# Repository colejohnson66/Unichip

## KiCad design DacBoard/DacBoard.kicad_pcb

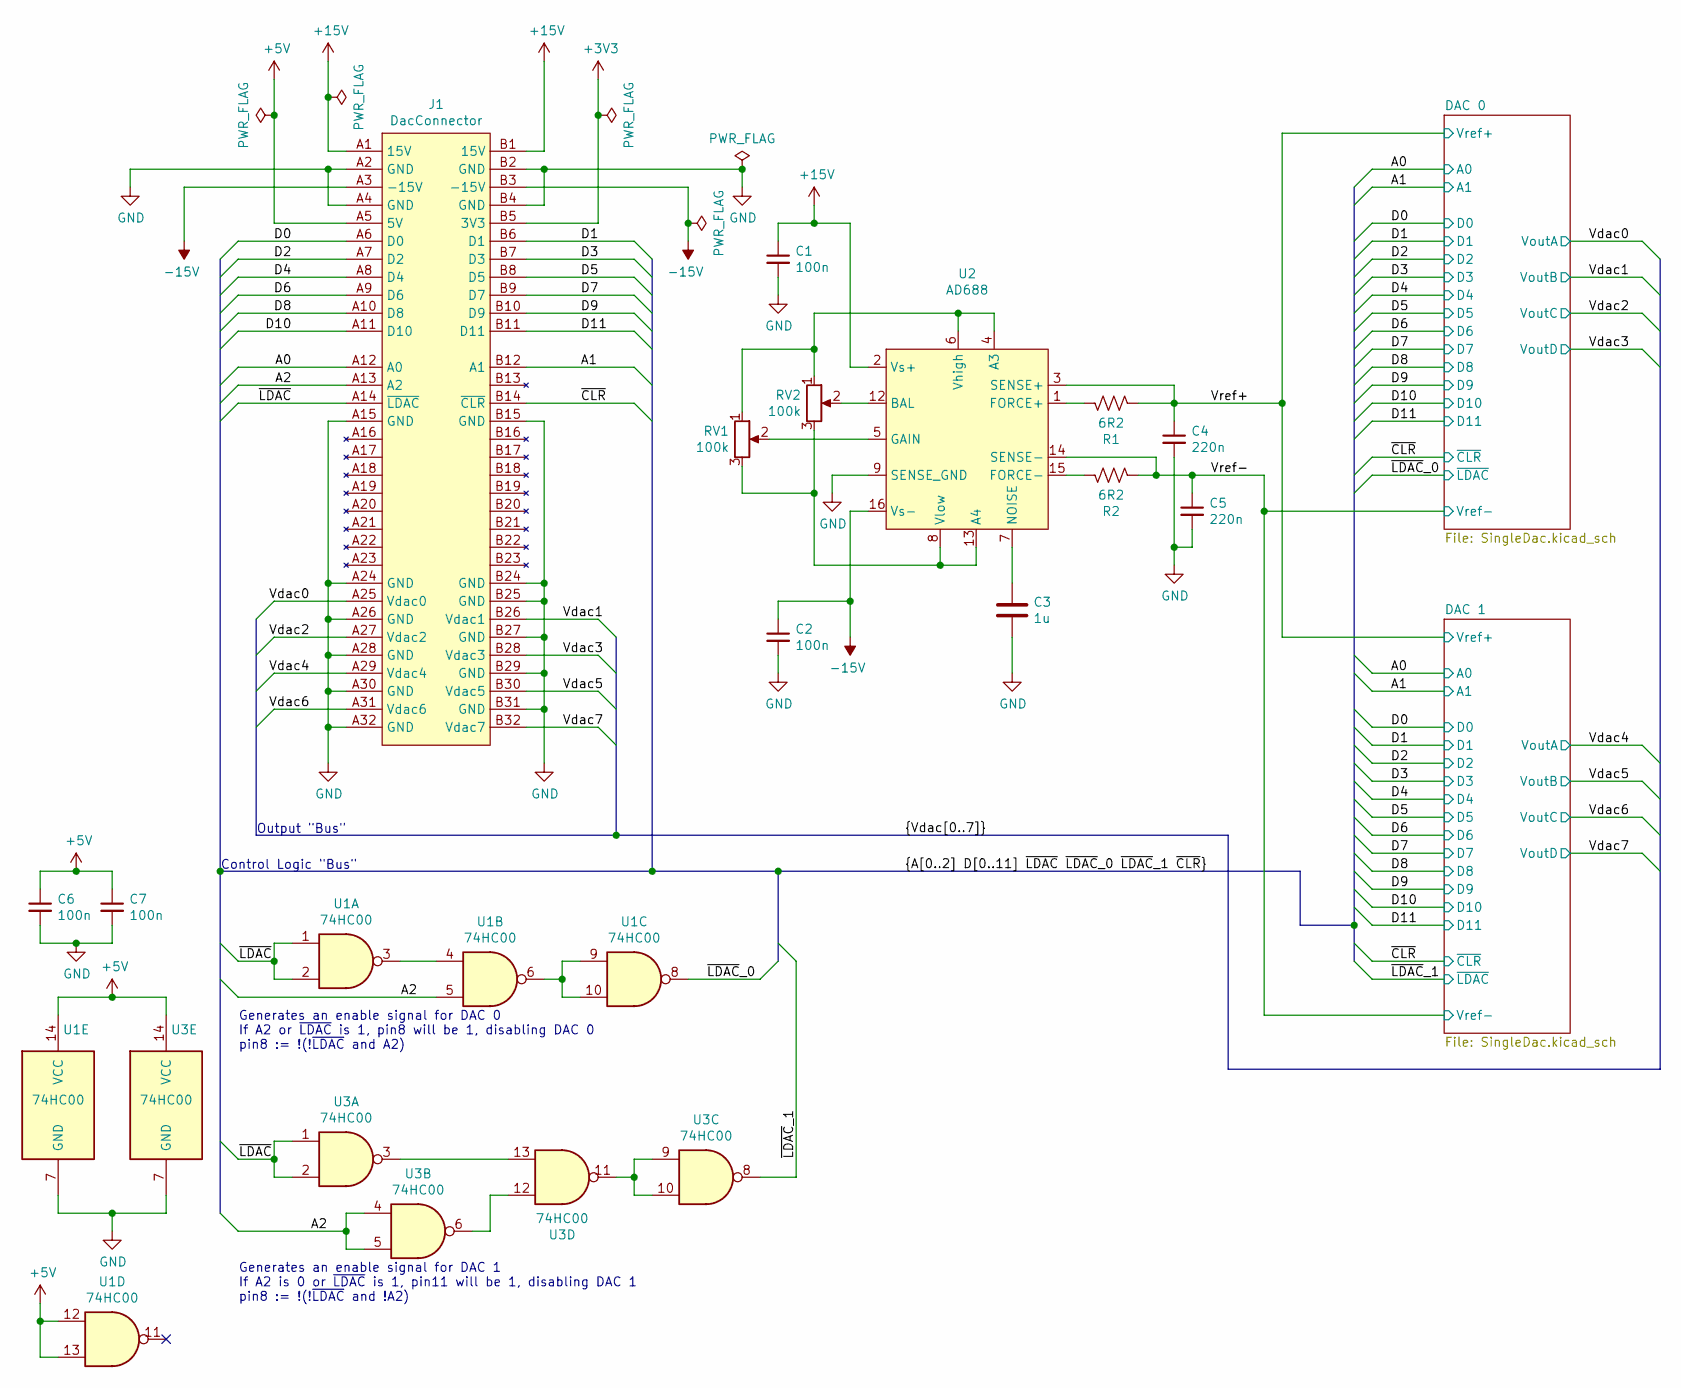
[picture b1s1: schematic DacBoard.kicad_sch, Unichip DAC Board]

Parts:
C1, C2, C6, C7: 100n; C_0805_2012Metric_Pad1.18x1.45mm_HandSolder
C3: 1u; C_0805_2012Metric_Pad1.18x1.45mm_HandSolder
C4, C5: 220n; C_0805_2012Metric_Pad1.18x1.45mm_HandSolder
J1: DacConnector; BUS_PCIexpress_x4
R1, R2: 6R2; R_0805_2012Metric_Pad1.20x1.40mm_HandSolder
RV1, RV2: 100k; Potentiometer_Bourns_TC33X_Vertical
U1, U3: 74HC00; SOIC-14_3.9x8.7mm_P1.27mm
U2: AD688; SOIC-16W_7.5x10.3mm_P1.27mm

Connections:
+3V3: J1.B5 (3V3)
+5V: C6.1, C7.1, J1.A5 (5V), U1.12, U1.13, U1.14 (VCC), U3.14 (VCC); also elsewhere on the board
+15V: C1.1, J1.A1 (15V), J1.B1 (15V), U2.2 (Vs+); also elsewhere on the board
-15V: C2.1, J1.A3 (-15V), J1.B3 (-15V), U2.16 (Vs-); also elsewhere on the board
/A0: J1.A12 (A0); also elsewhere on the board
/A1: J1.B12 (A1); also elsewhere on the board
/A2: J1.A13 (A2), U1.5, U3.4, U3.5
/D0: J1.A6 (D0); also elsewhere on the board
/D1: J1.B6 (D1); also elsewhere on the board
/D2: J1.A7 (D2); also elsewhere on the board
/D3: J1.B7 (D3); also elsewhere on the board
/D4: J1.A8 (D4); also elsewhere on the board
/D5: J1.B8 (D5); also elsewhere on the board
/D6: J1.A9 (D6); also elsewhere on the board
/D7: J1.B9 (D7); also elsewhere on the board
/D8: J1.A10 (D8); also elsewhere on the board
/D9: J1.B10 (D9); also elsewhere on the board
/D10: J1.A11 (D10); also elsewhere on the board
/D11: J1.B11 (D11); also elsewhere on the board
/Vdac0: J1.A25 (Vdac0); also elsewhere on the board
/Vdac1: J1.B26 (Vdac1); also elsewhere on the board
/Vdac2: J1.A27 (Vdac2); also elsewhere on the board
/Vdac3: J1.B28 (Vdac3); also elsewhere on the board
/Vdac4: J1.A29 (Vdac4); also elsewhere on the board
/Vdac5: J1.B30 (Vdac5); also elsewhere on the board
/Vdac6: J1.A31 (Vdac6); also elsewhere on the board
/Vdac7: J1.B32 (Vdac7); also elsewhere on the board
/Vref+: C4.1, R1.1, U2.3 (SENSE+); also elsewhere on the board
/Vref-: C5.1, R2.1, U2.14 (SENSE-); also elsewhere on the board
/~CLR: J1.B14 (~CLR); also elsewhere on the board
/~LDAC: J1.A14 (~LDAC), U1.1, U1.2, U3.1, U3.2
/~LDAC~_0: U1.8; also elsewhere on the board
/~LDAC~_1: U3.8; also elsewhere on the board
GND: C1.2, C2.2, C3.2, C4.2, C5.2, C6.2, C7.2, J1.A2 (GND), J1.A4 (GND), J1.A15 (GND), J1.A24 (GND), J1.A26 (GND), J1.A28 (GND), J1.A30 (GND), J1.A32 (GND), J1.B2 (GND), J1.B4 (GND), J1.B15 (GND), J1.B24 (GND), J1.B25 (GND), J1.B27 (GND), J1.B29 (GND), J1.B31 (GND), U1.7 (GND), U2.9 (SENSE_GND), U3.7 (GND); also elsewhere on the board
unnamed: C3.1, U2.7 (NOISE)
unnamed: R1.2, U2.1 (FORCE+)
unnamed: R2.2, U2.15 (FORCE-)
unnamed: RV1.1, RV2.1, U2.4 (A3), U2.6 (Vhigh)
unnamed: RV1.2, U2.5 (GAIN)
unnamed: RV1.3, RV2.3, U2.8 (Vlow), U2.13 (A4)
unnamed: RV2.2, U2.12 (BAL)
unnamed: U1.3, U1.4
unnamed: U1.6, U1.9, U1.10
unnamed: U3.3, U3.13
unnamed: U3.6, U3.12
unnamed: U3.9, U3.10, U3.11

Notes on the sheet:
Control Logic "Bus"
Generates an enable signal for DAC 0 If A2 or ~LDAC is 1, pin8 will be 1, disabling DAC 0 pin8 := !(!~LDAC and A2)
Generates an enable signal for DAC 1 If A2 is 0 or ~LDAC is 1, pin11 will be 1, disabling DAC 1 pin8 := !(!~LDAC and !A2)
Output "Bus"

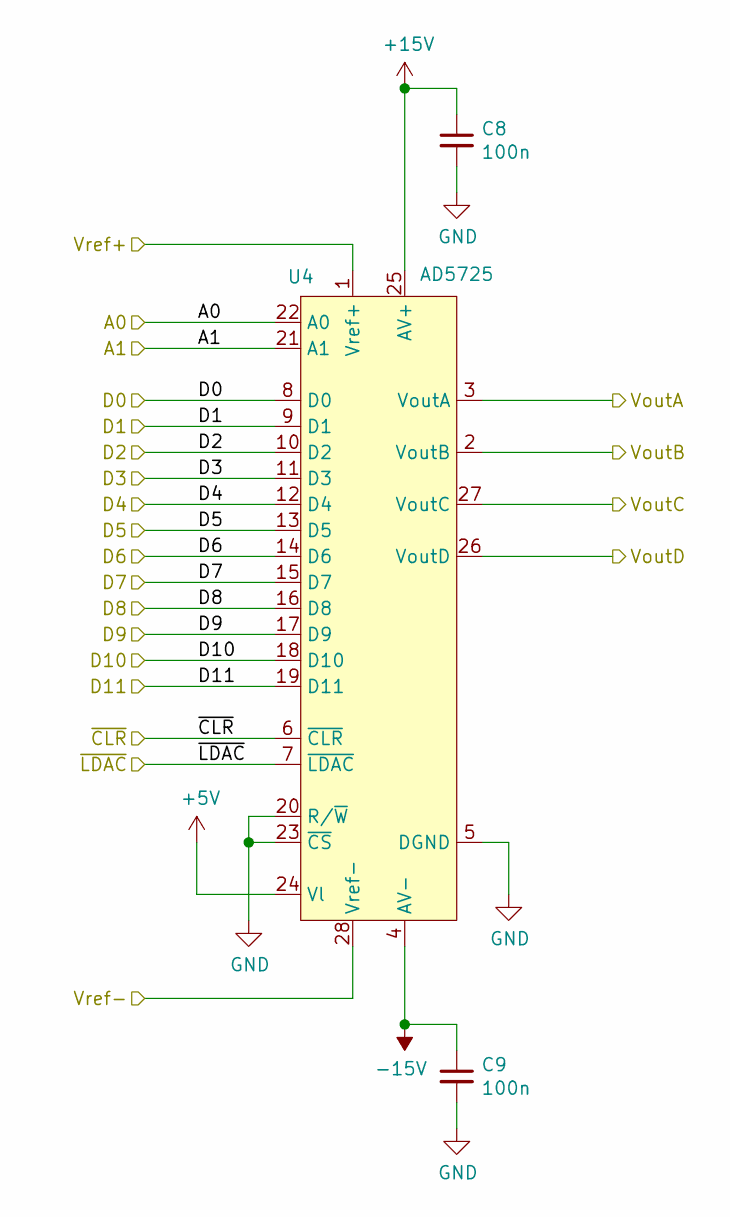
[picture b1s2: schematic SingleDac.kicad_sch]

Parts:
C8, C9: 100n; C_0805_2012Metric_Pad1.18x1.45mm_HandSolder
U4: AD5725; SSOP-28_5.3x10.2mm_P0.65mm

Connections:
+5V: U4.24 (Vl); also elsewhere on the board
+15V: C8.1, U4.25 (AV+); also elsewhere on the board
-15V: C9.1, U4.4 (AV-); also elsewhere on the board
/A0: U4.22 (A0); also elsewhere on the board
/A1: U4.21 (A1); also elsewhere on the board
/D0: U4.8 (D0); also elsewhere on the board
/D1: U4.9 (D1); also elsewhere on the board
/D2: U4.10 (D2); also elsewhere on the board
/D3: U4.11 (D3); also elsewhere on the board
/D4: U4.12 (D4); also elsewhere on the board
/D5: U4.13 (D5); also elsewhere on the board
/D6: U4.14 (D6); also elsewhere on the board
/D7: U4.15 (D7); also elsewhere on the board
/D8: U4.16 (D8); also elsewhere on the board
/D9: U4.17 (D9); also elsewhere on the board
/D10: U4.18 (D10); also elsewhere on the board
/D11: U4.19 (D11); also elsewhere on the board
/Vdac0: U4.3 (VoutA); also elsewhere on the board
/Vdac1: U4.2 (VoutB); also elsewhere on the board
/Vdac2: U4.27 (VoutC); also elsewhere on the board
/Vdac3: U4.26 (VoutD); also elsewhere on the board
/Vref+: U4.1 (Vref+); also elsewhere on the board
/Vref-: U4.28 (Vref-); also elsewhere on the board
/~CLR: U4.6 (~CLR); also elsewhere on the board
/~LDAC~_0: U4.7 (~LDAC); also elsewhere on the board
GND: C8.2, C9.2, U4.5 (DGND), U4.20 (R/~W), U4.23 (~CS); also elsewhere on the board

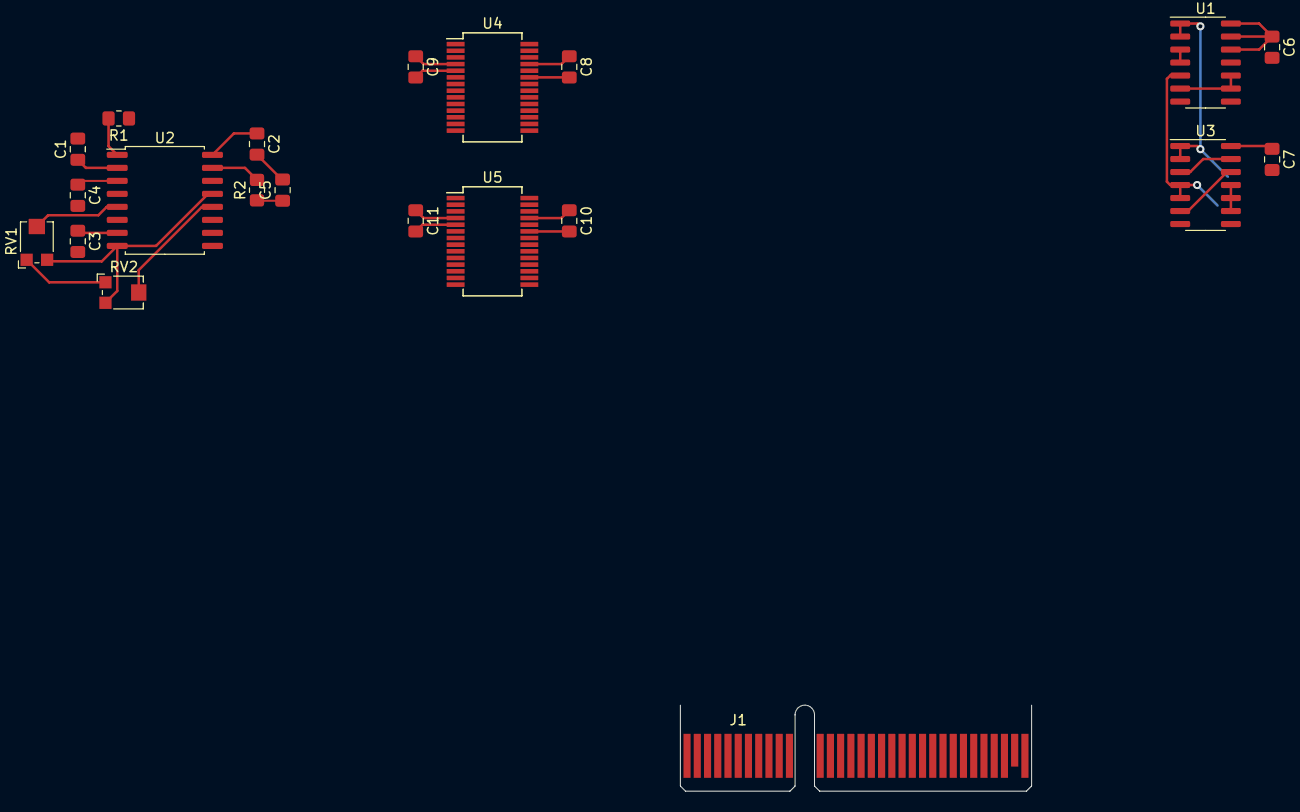
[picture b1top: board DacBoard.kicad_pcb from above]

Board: 2 copper layers, 21 parts (0 on the bottom side), 45 nets.

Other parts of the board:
C10, C11: 100n; C_0805_2012Metric_Pad1.18x1.45mm_HandSolder
U5: AD5725; SSOP-28_5.3x10.2mm_P0.65mm

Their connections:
+5V: U5.24 (Vl); also elsewhere on the board
+15V: C10.1, U5.25 (AV+); also elsewhere on the board
-15V: C11.1, U5.4 (AV-); also elsewhere on the board
/A0: U5.22 (A0); also elsewhere on the board
/A1: U5.21 (A1); also elsewhere on the board
/D0: U5.8 (D0); also elsewhere on the board
/D1: U5.9 (D1); also elsewhere on the board
/D2: U5.10 (D2); also elsewhere on the board
/D3: U5.11 (D3); also elsewhere on the board
/D4: U5.12 (D4); also elsewhere on the board
/D5: U5.13 (D5); also elsewhere on the board
/D6: U5.14 (D6); also elsewhere on the board
/D7: U5.15 (D7); also elsewhere on the board
/D8: U5.16 (D8); also elsewhere on the board
/D9: U5.17 (D9); also elsewhere on the board
/D10: U5.18 (D10); also elsewhere on the board
/D11: U5.19 (D11); also elsewhere on the board
/Vdac4: U5.3 (VoutA); also elsewhere on the board
/Vdac5: U5.2 (VoutB); also elsewhere on the board
/Vdac6: U5.27 (VoutC); also elsewhere on the board
/Vdac7: U5.26 (VoutD); also elsewhere on the board
/Vref+: U5.1 (Vref+); also elsewhere on the board
/Vref-: U5.28 (Vref-); also elsewhere on the board
/~CLR: U5.6 (~CLR); also elsewhere on the board
/~LDAC~_1: U5.7 (~LDAC); also elsewhere on the board
GND: C10.2, C11.2, U5.5 (DGND), U5.20 (R/~W), U5.23 (~CS); also elsewhere on the board

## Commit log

2021-02-03 added AD5725
2021-02-13 Added a DAC board connector (PCIe 1x)
2021-02-13 Changed DacConnector to be PCIe 4x
2021-02-13 Added AD688 and filled in schematic (ERC needs testing)
2021-02-13 Changed data bus to single wires
2021-02-14 Added bypass caps and moved PWR_FLAGs around
2021-02-14 Fixed description of enable signal generators
2021-02-14 Schematic finalized (for now); Begin PCB
2021-03-28 Added stub firmware based on RP2040
2021-03-28 minor VSCode settings tweaks
2021-03-28 Added a stub processor board with RPi Pico
2021-04-03 Working on PCB layout
